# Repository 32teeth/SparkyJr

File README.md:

-------------

# Introduction

**SparkyJr.** is a programmable RGB LED mod companion light up activation controller for arcade pushbuttons on gaming fightsticks.

The hardware is based on AVR microcontrollers and programmed via [AVR Studio](http://www.atmel.ca/microsite/atmel_studio6/) or the [Arduino IDE](http://arduino.cc/en/Main/Software)

**<span style="color:red">*note:*</span> please use Arduino IDE 1.0.6**

**SparkyJr.** in it's entirety is open source. Including hardware design, software implementation and libraries
***
##Software
#### Arduino

**SparkyJr.** Arduino based files are located in the *[arduino](https://github.com/32teeth/SparkyJr/tree/gh-pages/arduino/Sparky)* folder

This includes all the files required to upload to your specific AVR chipset.

**SparkyJr** only has one library dependency. We make use of the [EEPROMx](https://github.com/autohome/autohome-arduino/tree/master/libraries/EEPROMx) library

*for help on installing libraries into the Arduino IDE, please visit the [how to](http://arduino.cc/en/Guide/Libraries) on the Arduino site

#### Processing
**SparkyJr.** Processing based files are located in the *[processing](https://github.com/32teeth/SparkyJr/tree/gh-pages/processing)* folder

This includes all the files required to run the configurator.

#### Google Chrome App
**SparkyJr.**'s configurator is additionally available as a Google Chrome Application and is available unpackaged in the [google](https://github.com/32teeth/SparkyJr/tree/gh-pages/google) folder

***
##Hardware
#### Eagle CAD
All of the PCB design, schema and board layout files where designed in [CadSoft's Eagle Cad PCB](http://www.cadsoftusa.com/eagle-pcb-design-software/product-overview/?language=en) software.

The .sch and .brd files are available in the [eagle](https://github.com/32teeth/SparkyJr/tree/gh-pages/eagle) folder.

####SparkyJr. hardware variants
*all versions are currenlty supported in the new SparkyJr software and configurator*

|  v1 | v2 (pwm)  | v3 (ftdi) (32u4)  | *v4* (current)  | v4 (expansion) |
|---|---|---|---|---|
|retired|retired|deprecated|current release|expansion board|
|   |   |   |   |   |
|   |   |  ftdi [sch](https://github.com/32teeth/SparkyJr/blob/gh-pages/eagle/SparkyJr_v4FTDI.sch) [brd](https://github.com/32teeth/SparkyJr/blob/gh-pages/eagle/SparkyJr_v4FTDI.brd) |  [sch](https://github.com/32teeth/SparkyJr/blob/gh-pages/eagle/SparkySpecialK.sch) [brd](https://github.com/32teeth/SparkyJr/blob/gh-pages/eagle/SparkySpecialK.brd) | [sch](https://github.com/32teeth/SparkyJr/blob/gh-pages/eagle/SparkySpecialKExpansion.sch) [brd](https://github.com/32teeth/SparkyJr/blob/gh-pages/eagle/SparkySpecialKExpansion.brd)  |
|   |   |  32u4 [sch](https://github.com/32teeth/SparkyJr/blob/gh-pages/eagle/SparkyJr_v432u4.sch) [brd](https://github.com/32teeth/SparkyJr/blob/gh-pages/eagle/SparkyJr_v432u4.brd) |   |   |

***
## Arduino

Start up your Arduino IDE and open **Sparky.ino**
The only file you *need* to change settings in is the [setup.h](https://github.com/32teeth/SparkyJr/blob/gh-pages/arduino/Sparky/setup.h) file

to identify your board to the SparkyJr software, simply uncomment the right line
the comments in the code indicate the proper name

```
/*
** @define (DRIVER|LEO|UNO|JOY|RAZER)
** @desc DRIVER = Arduino WS2811 Shield
** @desc LEO = Arduino Leonardo
** @desc SPARKY = SparkyJrFTDI
** @desc UNO = Arduino UNO
** @desc JOY = Arduino Joystick Shield
** @desc RAZER = Razer Atrox Arcade Stick
*/
#define DRIVER
//#define LEO
//#define SPARKY
//#define UNO
//#define JOY
//#define RAZER
```
to identify your RGB LED type to the SparkyJr software, simply uncomment the right line

```
/*
** @define (ANODE|CATHODE)
** @desc ANODE = Common Anode RGB LEDs
** @desc CATHODE = Common Cathode RGB LEDs
*/
#define ANODE
//#define CATHODE
```
Complie and Run!

***
## Processing

if you are on a Mac, you're in luck. There is a packaged application available for you. Simply download the [SparkyOfficial.app](https://github.com/32teeth/SparkyJr/tree/gh-pages/processing/SparkyOfficial/SparkyOfficial/application.macosx/SparkyOfficial.app) file

if you are looking to run the application from source, simply download Processing and run the [SparkyOfficial.pde](https://github.com/32teeth/SparkyJr/blob/gh-pages/processing/SparkyOfficial/SparkyOfficial/SparkyOfficial.pde) file

***
Should you run into any trouble, or have further questions, feel free to reach out.

[ 32teeth](https://www.facebook.com/32teeth)

[ eugeneyevhen](https://twitter.com/eugeneyevhen)

[ SparkyJr](32teeth.github.io/SparkyJr)

[ 32teeth](http://ca.linkedin.com/in/32teeth)

***
# Thanks

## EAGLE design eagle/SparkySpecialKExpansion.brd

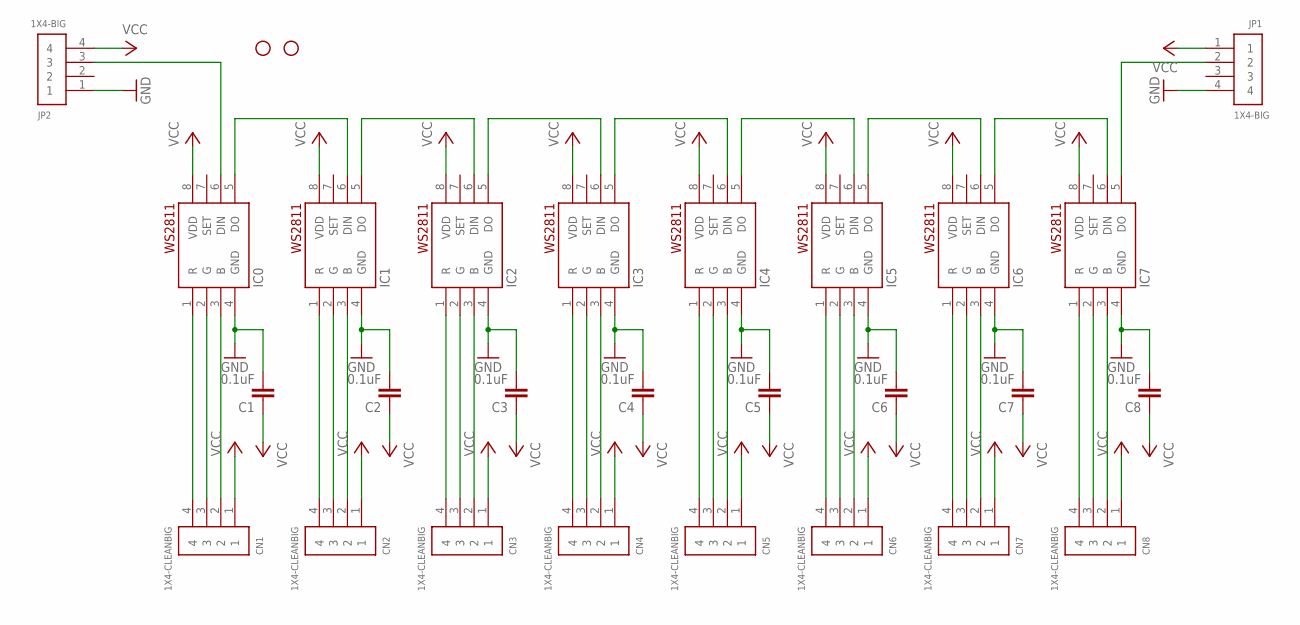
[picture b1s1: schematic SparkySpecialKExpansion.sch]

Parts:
C1, C2, C3, C4, C5, C6, C7, C8: 0.1uF; 0805
CN1, CN2, CN3, CN4, CN5, CN6, CN7, CN8: 1X4-CLEANBIG; 1X04-CLEANBIG
IC0, IC1, IC2, IC3, IC4, IC5, IC6, IC7: WS2811-SOP8; SO08-SKINNYPADS
JP1, JP2: 1X4-BIG; 1X04-BIG
JP3, JP4: STAND-OFF

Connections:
GND: C1.2, C2.2, C3.2, C4.2, C5.2, C6.2, C7.2, C8.2, IC0.4 (GND), IC1.4 (GND), IC2.4 (GND), IC3.4 (GND), IC4.4 (GND), IC5.4 (GND), IC6.4 (GND), IC7.4 (GND), JP1.4, JP2.1
unnamed: CN1.2, IC0.3 (B)
unnamed: CN1.3, IC0.2 (G)
unnamed: CN1.4, IC0.1 (R)
unnamed: CN2.4, IC1.1 (R)
unnamed: CN2.3, IC1.2 (G)
unnamed: CN2.2, IC1.3 (B)
unnamed: CN3.4, IC2.1 (R)
unnamed: CN3.3, IC2.2 (G)
unnamed: CN3.2, IC2.3 (B)
unnamed: CN4.4, IC3.1 (R)
unnamed: CN4.3, IC3.2 (G)
unnamed: CN4.2, IC3.3 (B)
unnamed: CN5.4, IC4.1 (R)
unnamed: CN5.3, IC4.2 (G)
unnamed: CN5.2, IC4.3 (B)
unnamed: CN6.4, IC5.1 (R)
unnamed: CN6.3, IC5.2 (G)
unnamed: CN6.2, IC5.3 (B)
unnamed: CN7.4, IC6.1 (R)
unnamed: CN7.3, IC6.2 (G)
unnamed: CN7.2, IC6.3 (B)
unnamed: CN8.4, IC7.1 (R)
unnamed: CN8.3, IC7.2 (G)
unnamed: CN8.2, IC7.3 (B)
unnamed: IC0.5 (DO), IC1.6 (DIN)
unnamed: IC1.5 (DO), IC2.6 (DIN)
unnamed: IC2.5 (DO), IC3.6 (DIN)
unnamed: IC3.5 (DO), IC4.6 (DIN)
unnamed: IC4.5 (DO), IC5.6 (DIN)
unnamed: IC5.5 (DO), IC6.6 (DIN)
unnamed: IC6.5 (DO), IC7.6 (DIN)
unnamed: IC7.5 (DO), JP1.2
unnamed: IC0.6 (DIN), JP2.3
VCC: C1.1, C2.1, C3.1, C4.1, C5.1, C6.1, C7.1, C8.1, CN1.1, CN2.1, CN3.1, CN4.1, CN5.1, CN6.1, CN7.1, CN8.1, IC0.8 (VDD), IC1.8 (VDD), IC2.8 (VDD), IC3.8 (VDD), IC4.8 (VDD), IC5.8 (VDD), IC6.8 (VDD), IC7.8 (VDD), JP1.1, JP2.4

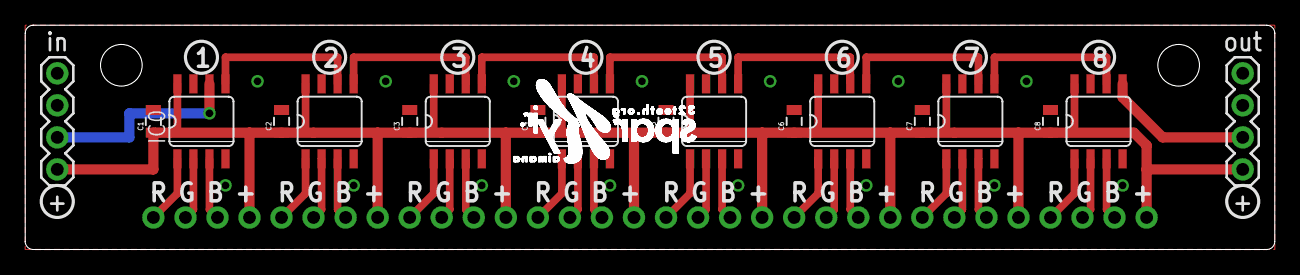
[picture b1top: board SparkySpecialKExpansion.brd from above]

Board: 2 copper layers, 99.1 x 17.8 mm, 28 parts (0 on the bottom side), 35 nets.

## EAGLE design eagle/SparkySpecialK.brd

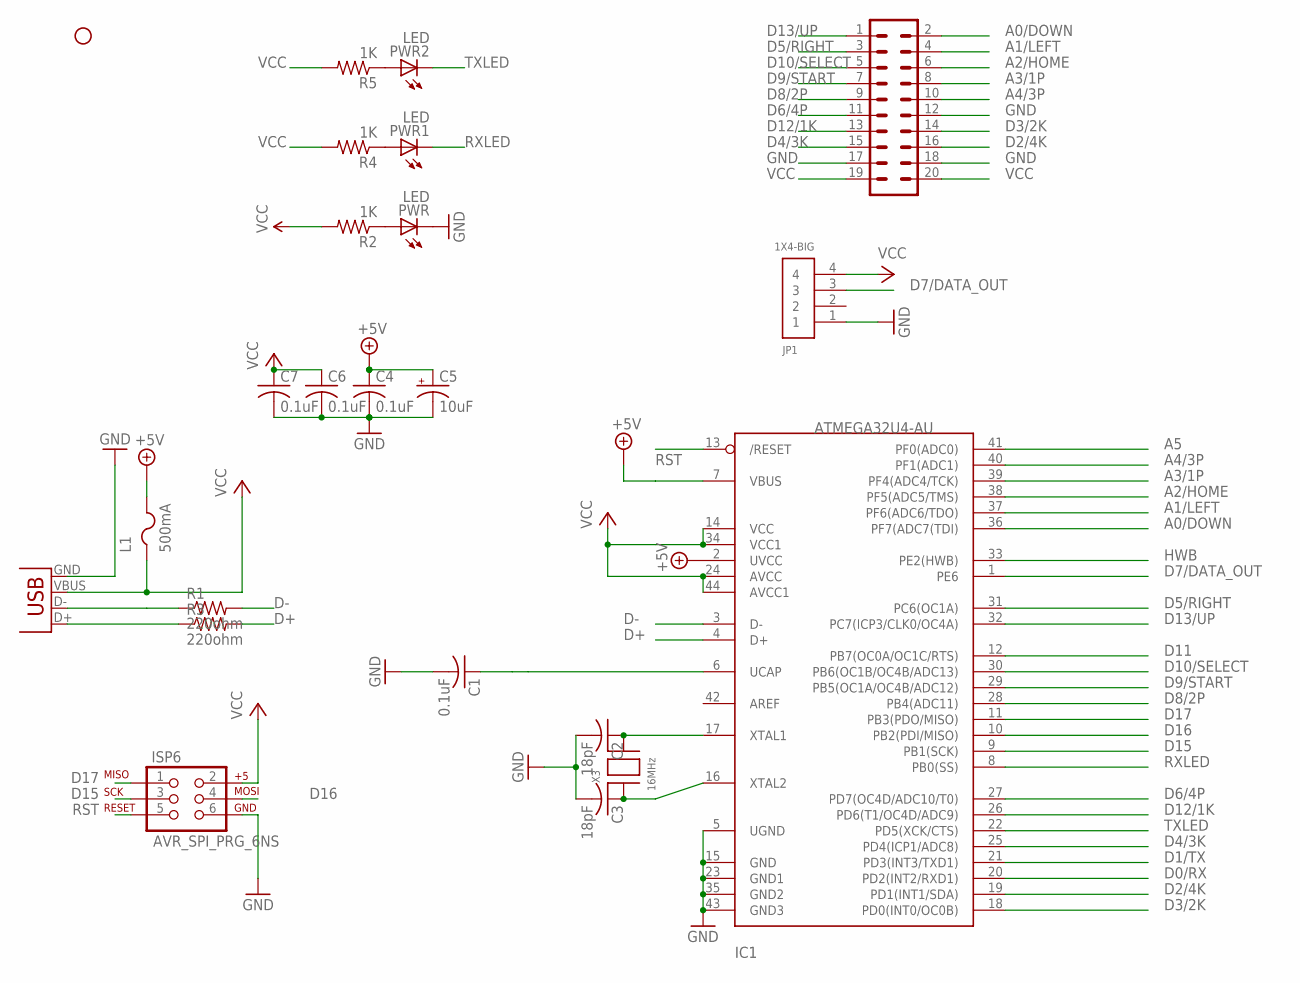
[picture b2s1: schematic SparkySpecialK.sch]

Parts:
C1, C4, C6, C7: 0.1uF; C0805K
C2, C3: 18pF; C0805K
C5: 10uF; A/3216-18R
CN1: MiniB USB; USB-MINIB
IC1: ATMEGA32U4-AU; TQFP44
ISP6: AVR_SPI_PRG_6NS; 2X3-NS
JP1: 1X4-BIG; 1X04-BIG
JP2: STAND-OFF
L1: 500mA; R1206
PWR, PWR1, PWR2: LED; CHIPLED_0805
R1, R3: 220ohm; R0805
R2, R4, R5: 1K; R0805
U$1: M10X2NOSILK; 2X10_NOSILK
X3: 16MHz; NX5032

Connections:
+5V: C4.1, C5.+, IC1.2 (UVCC), IC1.7 (VBUS), L1.2
A0/DOWN: IC1.36 (PF7(ADC7(TDI)), U$1.2
A1/LEFT: IC1.37 (PF6(ADC6/TDO)), U$1.4
A2/HOME: IC1.38 (PF5(ADC5/TMS)), U$1.6
A3/1P: IC1.39 (PF4(ADC4/TCK)), U$1.8
A4/3P: IC1.40 (PF1(ADC1)), U$1.10
A5: IC1.41 (PF0(ADC0))
D0/RX: IC1.20 (PD2(INT2/RXD1))
D1/TX: IC1.21 (PD3(INT3/TXD1))
D2/4K: IC1.19 (PD1(INT1/SDA)), U$1.16
D3/2K: IC1.18 (PD0(INT0/OC0B)), U$1.14
D4/3K: IC1.25 (PD4(ICP1/ADC8)), U$1.15
D5/RIGHT: IC1.31 (PC6(OC1A)), U$1.3
D6/4P: IC1.27 (PD7(OC4D/ADC10/T0)), U$1.11
D7/DATA_OUT: IC1.1 (PE6), JP1.3
D8/2P: IC1.28 (PB4(ADC11)), U$1.9
D9/START: IC1.29 (PB5(OC1A/OC4B/ADC12)), U$1.7
D10/SELECT: IC1.30 (PB6(OC1B/OC4B/ADC13)), U$1.5
D11: IC1.12 (PB7(OC0A/OC1C/RTS))
D12/1K: IC1.26 (PD6(T1/OC4D/ADC9)), U$1.13
D13/UP: IC1.32 (PC7(ICP3/CLK0/OC4A)), U$1.1
D15: IC1.9 (PB1(SCK)), ISP6.3
D16: IC1.10 (PB2(PDI/MISO)), ISP6.4
D17: IC1.11 (PB3(PDO/MISO)), ISP6.1
D+: IC1.4 (D+), R3.2
D-: IC1.3 (D-), R1.2
GND: C1.2, C2.2, C3.2, C4.2, C5.-, C6.2, C7.2, CN1.GND, IC1.5 (UGND), IC1.15 (GND), IC1.23 (GND1), IC1.35 (GND2), IC1.43 (GND3), ISP6.6, JP1.1, PWR.C, U$1.12, U$1.17, U$1.18
HWB: IC1.33 (PE2(HWB))
unnamed: PWR.A, R2.1
unnamed: CN1.D+, R3.1
unnamed: C1.1, IC1.6 (UCAP)
unnamed: CN1.D-, R1.1
unnamed: PWR1.A, R4.1
unnamed: PWR2.A, R5.1
unnamed: C2.1, IC1.17 (XTAL1), X3.P$2
unnamed: C3.1, IC1.16 (XTAL2), X3.P$1
RST: IC1.13 (/RESET), ISP6.5
RXLED: IC1.8 (PB0(SS)), PWR1.C
TXLED: IC1.22 (PD5(XCK/CTS)), PWR2.C
VCC: C6.1, C7.1, CN1.VBUS, IC1.14 (VCC), IC1.24 (AVCC), IC1.34 (VCC1), IC1.44 (AVCC1), ISP6.2, JP1.4, L1.1, R2.2, R4.2, R5.2, U$1.19, U$1.20

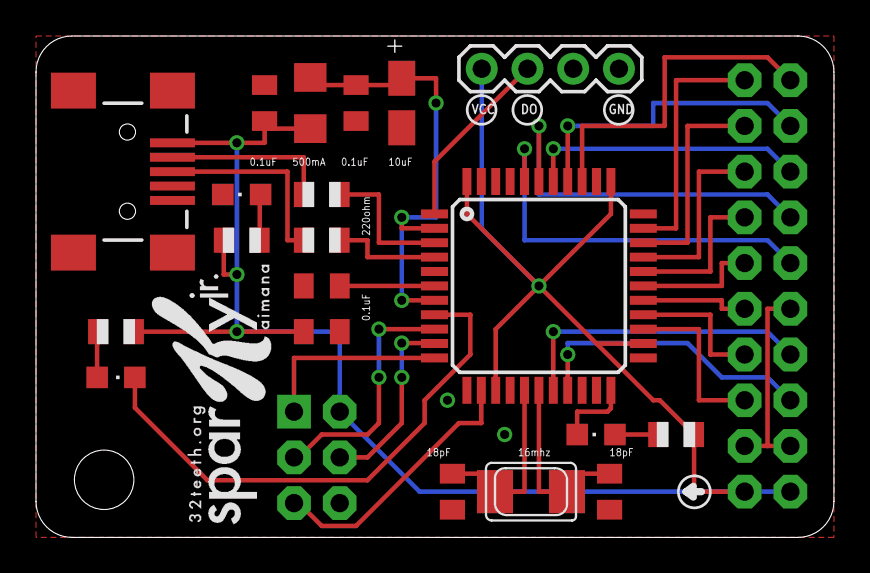
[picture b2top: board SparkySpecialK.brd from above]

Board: 2 copper layers, 44.3 x 27.9 mm, 23 parts (0 on the bottom side), 35 nets.

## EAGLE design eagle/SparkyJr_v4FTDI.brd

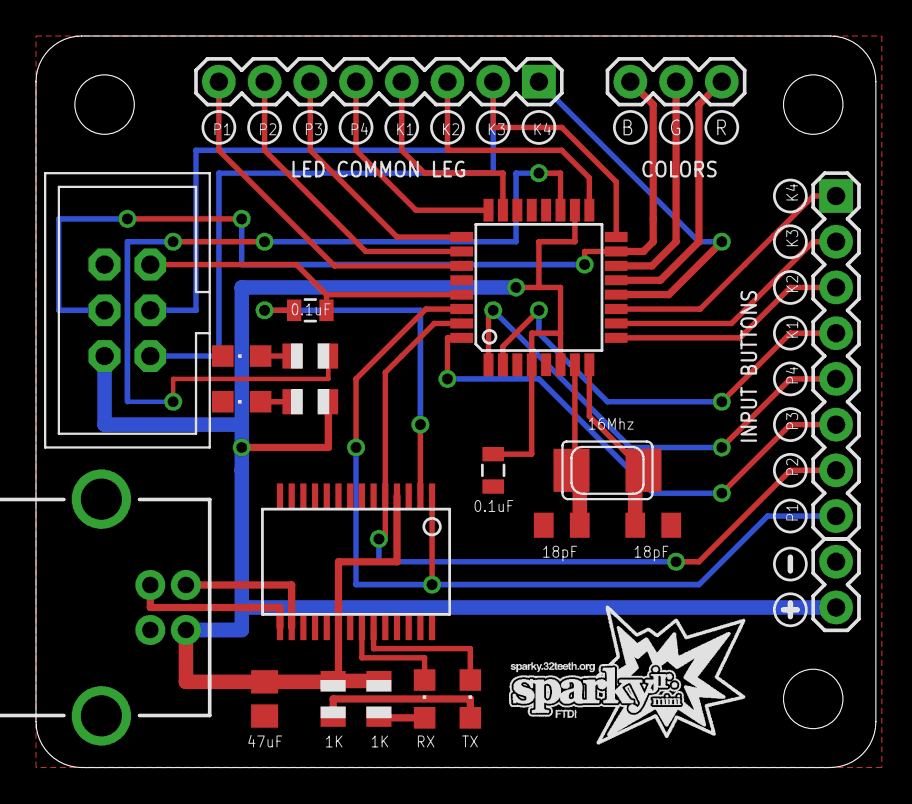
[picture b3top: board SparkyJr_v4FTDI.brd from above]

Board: 2 copper layers, 46.7 x 40.6 mm, 25 parts (0 on the bottom side), 34 nets.

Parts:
C1, C2: 0.1uF; 0805
C3, C5: 18pF; C0805K
C4: 47uF; C0805
COMMON: 1X08
CONFIG: LED; CHIPLED_0805
IC2: FT232RLSSOP; SSOP28DB
IN: 1X02
INPUT: 1X08
ISP6: PINHD-2X3THM; ISP6
JP1, JP2, JP3: STAND-OFF
PWR: LED; CHIPLED_0805
R1, R3: 100Ohm; R0805
R2, R4: 1K; R0805
RGB2: 1X03
RXLED: Blue; CHIPLED_0805
TXLED: Blue; CHIPLED_0805
U1: ATMEGA328P; TQFP32-08
X1: USBPTH; USB-B-PTH
X3: 16MHz; NX5032

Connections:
BLUE: ISP6.4, RGB2.1, U1.15
C1: COMMON.8, U1.27
C2: COMMON.7, U1.26
C3: COMMON.6, U1.25
C4: COMMON.5, U1.24
C5: COMMON.4, U1.23
C6: COMMON.3, ISP6.3, U1.17
C7: COMMON.2, ISP6.1, U1.16
C8: COMMON.1, U1.12
CONFIG: R4.2, U1.19
D+: IC2.15, X1.D+
D-: IC2.16, X1.D-
DTR: C1.1, IC2.2
GND: C2.1, C3.2, C4.2, C5.2, CONFIG.C, IC2.7, IC2.11, IC2.18, IC2.21, IC2.25, IC2.26, IN.2, ISP6.6, PWR.C, U1.3, U1.5, U1.21, U1.28, X1.GND
GREEN: RGB2.2, U1.14
K1: INPUT.4, U1.2
K2: INPUT.3, U1.9
K3: INPUT.2, U1.10
K4: INPUT.1, U1.11
unnamed: PWR.A, R2.1
unnamed: CONFIG.A, R4.1
unnamed: R3.1, RXLED.A
unnamed: R1.1, TXLED.A
P3: INPUT.6, U1.32
P4: INPUT.5, U1.1
RED: RGB2.3, U1.13
RES1: C3.1, U1.7, X3.P$2
RES2: C5.1, U1.8, X3.P$1
RESET: C1.2, ISP6.5, U1.29
RX: IC2.22, RXLED.C
RX-P2: IC2.5, INPUT.7, U1.31
TX: IC2.23, TXLED.C
TX-P1: IC2.1, INPUT.8, U1.30
VCC: C2.2, C4.1, IC2.4, IC2.20, IN.1, ISP6.2, R1.2, R2.2, R3.2, U1.4, U1.6, U1.18, X1.VBUS

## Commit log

2014-01-21 Sparky Jr initial homepage commit
2014-01-22 Commit of redirect
2014-01-22 Changed
2014-01-22 Big Upload
2014-01-23 created crossfader
2014-01-23 updated video
2014-01-23 Added Poster
2014-01-24 updated colour fading option
2014-01-27 Added modes
2014-01-29 Updated Several Components
2014-01-29 New Video
2014-01-29 Video update
2014-01-29 added fonts
2014-01-29 edit
2014-01-29 video
2014-01-29 removed title
2014-01-30 updated home page
2014-01-30 added poster to video
2014-01-30 100 height for iPad
2014-01-30 release
2014-01-30 again
2014-01-30 changed CDN
2014-01-31 Sparky Official
2014-02-03 added colour picker and svg
2014-02-03 added com
2014-02-04 Added WS2811 Driver functionality
2014-02-04 Update Skrollr
2014-02-04 updated timing
2014-02-08 updagtes
2014-02-10 updated videos
2014-02-11 Added Analytics
2014-02-13 Chrome App and iOS
2014-02-13 Chrome APp
2014-02-14 Serial Connection via Chrome Extension
2014-02-15 ooooo svg and canvas
2014-02-18 Updating Google App
2014-02-18 updated congas
2014-02-18 updated google app
2014-03-05 added serial functionality
2014-03-12 added eagle and sketch up
2014-03-20 updates to presentation
2014-03-21 updated markdown
2014-03-21 resized images
2014-03-21 updates to read me
2014-03-24 updated sketch
2014-03-27 added stuff
2014-03-31 updated connections
2014-03-31 pin change for special
2014-04-08 reset iOS project
2014-04-24 updated ardunio code
2014-04-24 added doge
2014-04-27 final updates
2016-02-02 updates setup
2016-02-02 merged markdown

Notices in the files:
parts and their libraries:
SparkFun-Connectors: Licensing: CC v3.0 Share-Alike You are welcome to use this library for commercial purposes.
